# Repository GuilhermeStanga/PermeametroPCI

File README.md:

# PermeametroPCI
Desenvolvido com KiCad

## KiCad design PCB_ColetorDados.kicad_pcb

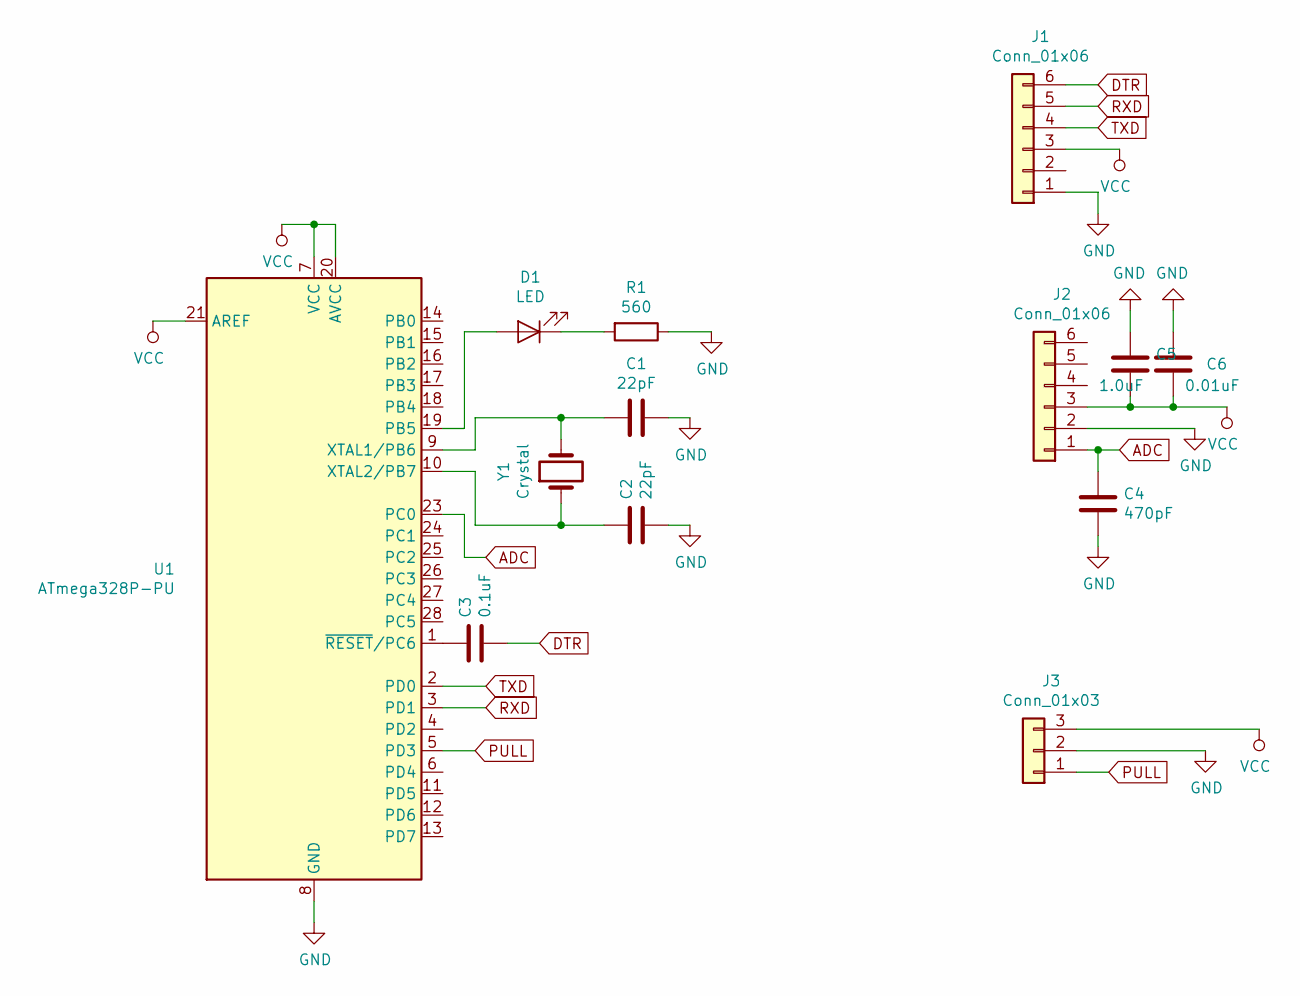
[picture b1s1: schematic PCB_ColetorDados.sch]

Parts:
C1, C2: 22pF; C_Disc_D3.4mm_W2.1mm_P2.50mm
C3: 0.1uF; C_Disc_D3.4mm_W2.1mm_P2.50mm
C4: 470pF; C_Disc_D3.4mm_W2.1mm_P2.50mm
C5: 1.0uF; C_Disc_D3.4mm_W2.1mm_P2.50mm
C6: 0.01uF; C_Disc_D3.4mm_W2.1mm_P2.50mm
D1: LED; LED_Oval_W5.2mm_H3.8mm
J1: Conn_01x06; PinSocket_1x06_P2.54mm_Vertical
J2: Conn_01x06; PinHeader_1x06_P2.54mm_Vertical
J3: Conn_01x03; PinSocket_1x03_P2.54mm_Vertical
R1: 560; R_Axial_DIN0309_L9.0mm_D3.2mm_P15.24mm_Horizontal
U1: ATmega328P-PU; DIP254P762X457-28
Y1: Crystal; Crystal_HC49-U_Vertical

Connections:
ADC: C4.1, J2.1, U1.23 (PC0)
DTR: C3.2, J1.6
GND: C1.1, C2.2, C4.2, C5.1, C6.1, J1.1, J2.2, J3.2, R1.1, U1.8 (GND), U1.22 (GND)
unnamed: C1.2, U1.9 (XTAL1/PB6), Y1.2
unnamed: C2.1, U1.10 (XTAL2/PB7), Y1.1
unnamed: C3.1, U1.1 (~RESET~/PC6)
unnamed: D1.1 (K), R1.2
unnamed: D1.2 (A), U1.19 (PB5)
PULL: J3.1, U1.5 (PD3)
RXD: J1.5, U1.3 (PD1)
TXD: J1.4, U1.2 (PD0)
VCC: C5.2, C6.2, J1.3, J2.3, J3.3, U1.7 (VCC), U1.20 (AVCC), U1.21 (AREF)

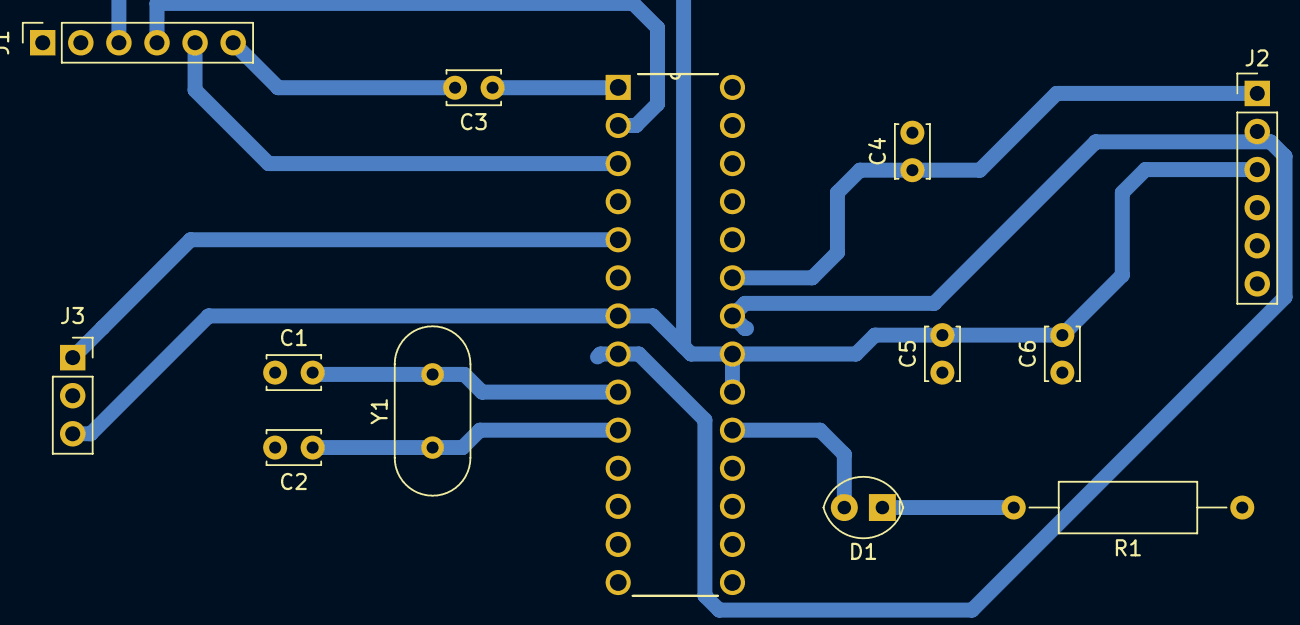
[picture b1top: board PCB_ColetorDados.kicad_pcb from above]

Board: 2 copper layers, 13 parts (0 on the bottom side), 12 nets.

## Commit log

2020-03-01 Commit Inicial
